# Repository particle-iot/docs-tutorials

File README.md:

# docs-tutorials

Tutorials, sample code, and sample designs used in the documentation [docs.particle.io](https://docs.particle.io).

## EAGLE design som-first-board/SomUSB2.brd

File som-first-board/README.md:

# SoM First Board

The tutorial can be found here: [https://docs.particle.io/tutorials/hardware-projects/som-first-board/](https://docs.particle.io/tutorials/hardware-projects/som-first-board/)

This repository contains the Eagle design files for the board used in the example.

- SomUSB2.sch - Schematic file for EagleCAD
- SomUSB2.brd - Board file for EagleCAD
- schematic.pdf - Schematic (PDF)
- board.pdf - Board (PDF)
- SomUSB1.lbr - Eagle library file with all of the parts used in the design
- SomUSB2v2.zip - Gerber files

### Version History

#### 2024-01-22 (v3)

- M.2 pin 40 should be D3 and M.2 pin 42 should be D2. These were reversed previously, however
this sample board does not use the pins.

#### 2020-03-30 (v2)

- Changed R8 from 158K to 150K to change 3V7 to 3V8. The voltage increase to 3.875V adds an extra safety margin for some modem modules.

#### 2019-10-24

- Updated M.2 standoff

#### 2019-05-20

- Initial version

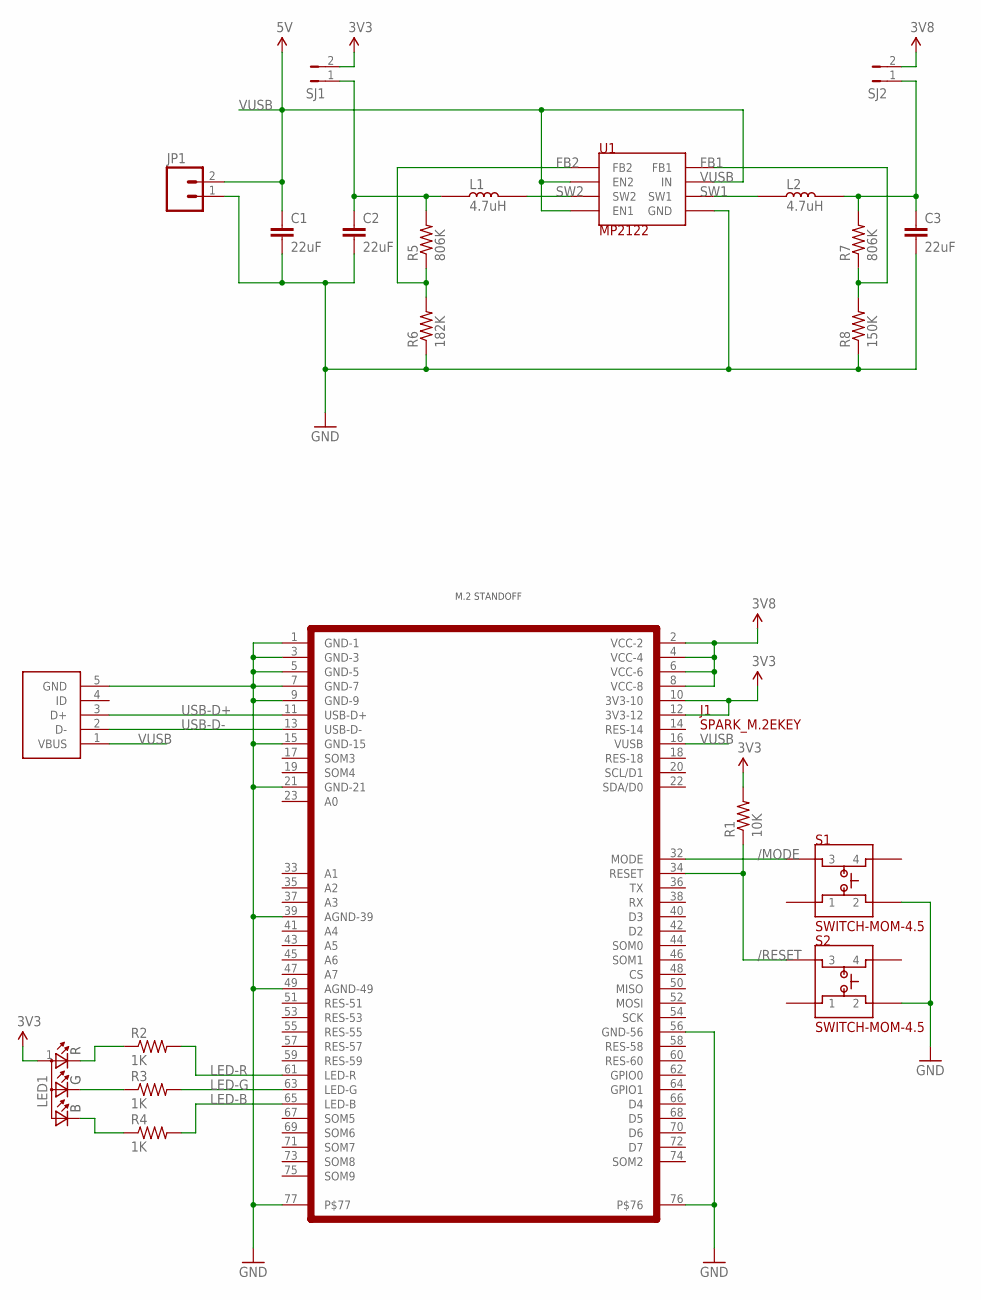
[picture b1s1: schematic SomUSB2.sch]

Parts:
C1, C2, C3: 22uF; 0805
J1: SPARK_M.2EKEY; SPARK_M.2EKEY-LESS-CREAM
JP1: M02PTH; 1X02
L1, L2: 4.7uH; 1008-BOURNS
LED1: LED-RGB-CREE-SMD
R1: 10K; 0603-RES
R2, R3, R4: 1K; 0603-RES
R5, R7: 806K; 0603-RES
R6: 182K; 0603-RES
R8: 150K; 0603-RES
S1, S2: SWITCH-MOM-4.5
SJ1, SJ2: JUMPER-PTH-2-NO; PTH-JUMPER-2-NO_NO_SILK
U1: MP2122; TSOT23-8-MPS
U$1: M2-STANDOFF
U$3: USB-MICRO-B-SOCKET-AMPHENOL; USB-B-SMT-AMPHENOL

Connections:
3V3: J1.10 (3V3-10), J1.12 (3V3-12), LED1.1 (A), R1.2, SJ1.2
3V3-REG: C2.1, L1.1, R5.2, SJ1.1
3V8: J1.2 (VCC-2), J1.4 (VCC-4), J1.6 (VCC-6), J1.8 (VCC-8), SJ2.2
3V8-REG: C3.1, L2.2, R7.2, SJ2.1
/MODE: J1.32 (MODE), S1.3
/RESET: J1.34 (RESET), R1.1, S2.3
FB1: R7.1, R8.2, U1.8 (FB1)
FB2: R5.1, R6.2, U1.1 (FB2)
GND: C1.2, C2.2, C3.2, J1.1 (GND-1), J1.3 (GND-3), J1.5 (GND-5), J1.7 (GND-7), J1.9 (GND-9), J1.15 (GND-15), J1.21 (GND-21), J1.39 (AGND-39), J1.49 (AGND-49), J1.56 (GND-56), J1.76, J1.77, JP1.1, R6.1, R8.1, S1.2, S2.2, U1.5 (GND), U$3.5 (GND)
LED-B: J1.65 (LED-B), R4.2
LED-G: J1.63 (LED-G), R3.2
LED-R: J1.61 (LED-R), R2.2
unnamed: LED1.3 (G), R3.1
unnamed: LED1.4 (R), R2.1
unnamed: LED1.2 (B), R4.1
SW1: L2.1, U1.6 (SW1)
SW2: L1.2, U1.3 (SW2)
USB-D+: J1.11 (USB-D+), U$3.3 (D+)
USB-D-: J1.13 (USB-D-), U$3.2 (D-)
VUSB: C1.1, J1.16 (VUSB), JP1.2, U1.2 (EN2), U1.4 (EN1), U1.7 (IN), U$3.1 (VBUS)

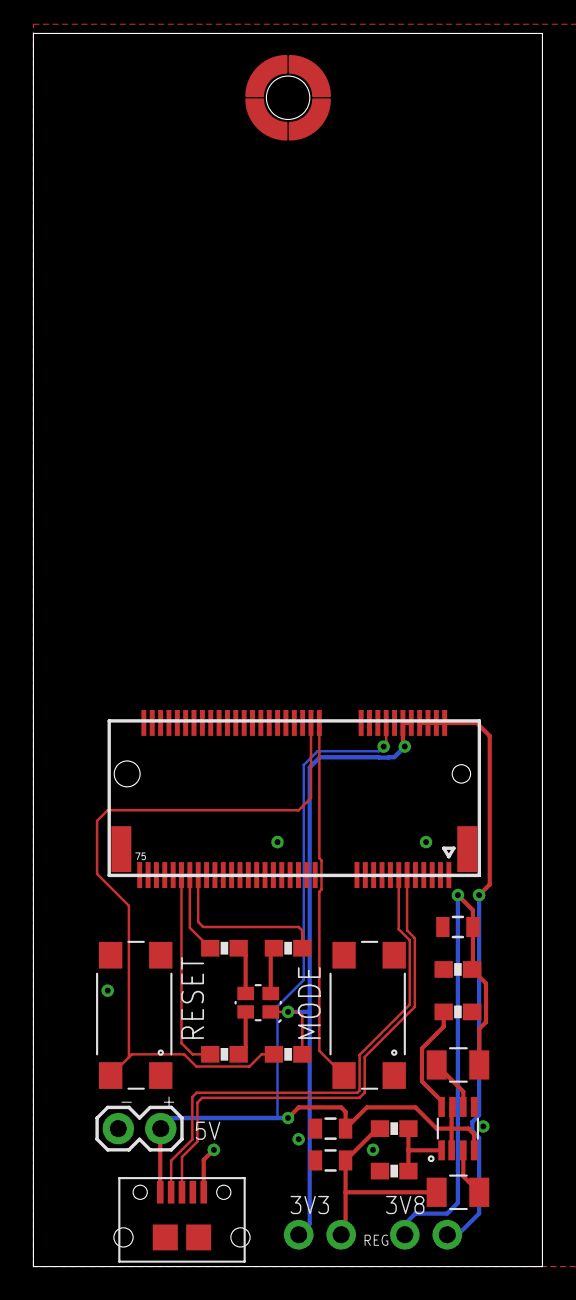
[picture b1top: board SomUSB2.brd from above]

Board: 2 copper layers, 30.5 x 73.8 mm, 23 parts (0 on the bottom side), 20 nets.

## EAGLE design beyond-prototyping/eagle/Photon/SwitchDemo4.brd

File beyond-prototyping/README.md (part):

# Upping your prototyping game

*Going from solderless breadboards to SMD components across Particle devices*

### Solderless breadboards 1

One of the most common ways to start building your project is to use a solderless breadboard. Here's my switch demo circuit in pure prototyping mode. There's an [RGB LED](https://www.sparkfun.com/products/10821) and an [LED button](https://www.sparkfun.com/products/10440) to the right of the Argon. This version uses long flexible wires, which are easy to set up and are easily reusable.

This is the schematic for the circuit:

Because the LED button switch pins don't line up with the holes on a solderless breadboard (0.1"), there's a [small adapter board](https://www.sparkfun.com/products/10467).

#### Bill of Materials (BOM)

| Quan | Item | Example | Price | 
| :--: | :--- | :--- | ---: |
| 1 | LED tactile button | [SparkFun](https://www.sparkfun.com/products/10440) | $2.10 |
| 1 | Button adapter | [SparkFun](https://www.sparkfun.com/products/10467) | $1.50 | 
| 1 | RGB LED | [SparkFun](https://www.sparkfun.com/products/10821) | $2.05 |
| 2 | 10 ohm resistor | | | 
| 2 | 100 ohm resistor | | |

### Solderless breadboards 2

One way to dress up your project is to switch to solid wires. It's a bit more work, but it certainly looks more professional and is good for projects you want to keep as-is.

I used a combination of [pre-formed wires](https://www.amazon.com/gp/product/B07WLPN929/ref=ppx_yo_dt_b_search_asin_title) and wires I cut, stripped, and bent to length from a [SparkFun hookup wire kit](https://www.sparkfun.com/products/11367).

### Perma-Proto

Once you've built and tested your solderless breadboard with solid wires, the next step up is an [Adafruit Perma-Proto](https://www.adafruit.com/product/1609) board. It has the same wiring as a solderless breadboard, but you solder the wires in place.

Resist the temptation to solder your device in place. Always use sockets, otherwise it's really a pain to troubleshoot or swap out the device if a problem occurs.

- Gen 3 feather (Argon, Boron, Xenon): 1x [12-pin](https://www.digikey.com/product-detail/en/sullins-connector-solutions/PPTC121LFBN-RC/S6100-ND/807231), 1x [16-pin](https://www.digikey.com/product-detail/en/sullins-connector-solutions/PPTC161LFBN-RC/S7014-ND/810154)
- Photon: 2x [12-pin](https://www.digikey.com/product-detail/en/sullins-connector-solutions/PPTC121LFBN-RC/S6100-ND/807231)
- Electron: 2x [18-pin](https://www.digikey.com/product-detail/en/sullins-connector-solutions/PPTC181LFBN-RC/S7016-ND/810156)

Note that you should use these headers or ones like them. The spacing between rows is not the same as most IC sockets. Plus, the pins on Particle devices are square, not the flat like IC chip leads, and wouldn't fit securely in an IC socket.

All you need to do is transfer over the component and wires and solder them to the board!

### Feather prototyping board

One of the nice features of the Gen 3 prototyping devices is the use of the [Adafruit Feather form-factor](https://learn.adafruit.com/adafruit-feather/feather-specification). Not only does this allow the devices to be easily swapped, but there are a large number of accessories like displays, GPS modules, and sensors already built in the Feather form-factor. Using a doubler, tripler, or quadrupler, you can add these to your project with no loose wires and no soldering!

However, sometimes you want something a little more custom. In this version, instead of using a big perma-proto board, I used a little FeatherWing solder prototype board. This is one in a Feather Doubler with an Argon:

And the board itself:

### Feather PTH board (through-hole components)

While the previous soldered boards all work fine, you can really make things look professional with a custom printed circuit board. This one uses hand-soldered through-hole components. It's referred to a PTH, plated through-hole.

I created the board schematic in [Eagle CAD](https://www.autodesk.com/products/eagle/overview). This small two-layer board can be done in the free version of Eagle CAD. The various schematic and board files are in the **eagle** directory in the Github repository.

The other part is creating the board file, which includes the actual placement of the components and the traces, which take the place of the wires. Here's by board file in Eagle.

I ordered these board from [OshPark](https://oshpark.com). 

Here are the components soldered in place. It's way faster to solder the components onto a circuit board than mess with all of the individual wires. And it looks so neat and clean!

### Feather SMD components board

The next step up is to switch to use SMD (surface mount device) components. The switch button is still through-hole soldered, but the resistors and LED are SMD. 

As your designs get more complex, being able to use smaller SMD components saves space and is actually easier than hand soldering once you get the hang of it. Also, many modern ICs are only available in SMD form-factor. The SMD RGB LED in this design is significantly less expensive than the PTH LED used above ($0.19 vs. $2.05).

The SMD LED uses different current-limiting resistors but the schematic is otherwise the same.

In order to assemble a SMD board, you'll use solder paste. I like this kind in a little syringe. This is [low-temperature solder paste](https://www.amazon.com/gp/product/B017RSGPI8/ref=ppx_yo_dt_b_search_asin_title), which is easy to work with and is lead-free.

Like the previous board, I ordered it from [OshPark](https://oshpark.com). Using the small syringe tip I put a little dot of solder on all of the SMD pads.

The next step is to place the components on the board. I like to use forceps and a dental pick. Some people prefer tweezers.

The the board goes into the reflow oven. This is an inexpensive T-962 which works fine for simple boards. 

There are a number of DIY techniques including using a skillet or baking them in a toaster oven, but using a real reflow oven is more accurate.

And here's the board after reflow soldering:

#### Bill of Materials (BOM)

| Quan | Item | Example | Price | 
| :--: | :--- | :--- | ---: |
| 1 | LED tactile button | [SparkFun](https://www.sparkfun.com/products/10440) | $2.10 |
| 1 | RGB LED | [Cree CLMVC-FKA-CL1D1L71BB7C3C3](https://www.digikey.com/product-detail/en/cree-inc/CLMVC-FKA-CL1D1L71BB7C3C3/CLMVC-FKA-CL1D1L71BB7C3C3CT-ND/9094273) | $0.19 |
|   | Male Header Pins | [Sullins PRPC040SAAN-RC](https://www.digikey.com/product-detail/en/PRPC040SAAN-RC/S1011EC-40-ND/2775214) |  |
| 2 | 33 ohm resistor 0603 | [Panasonic](https://www.digikey.com/product-detail/en/panasonic-electronic-components/ERJ-3EKF33R0V/P33.0HCT-ND/1746765) | | 
| 2 | 68 ohm resistor 0603 | [Panasonic](https://www.digikey.com/product-detail/en/panasonic-electronic-components/ERJ-3EKF68R0V/P68.0HCT-ND/1746805) | |

### Wing under-mount board

You don't need to make your boards into the actual FeatherWing form-factor. You can make an under-mount board as well. This is handy for larger designs. 

The schematic is the same, but the Eagle board layout is different:

#### Bill of Materials (BOM)

| Quan | Item | Example | Price | 
| :--: | :--- | :--- | ---: |
| 1 | LED tactile button | [SparkFun](https://www.sparkfun.com/products/10440) | $2.10 |
| 1 | RGB LED | [Cree CLMVC-FKA-CL1D1L71BB7C3C3](https://www.digikey.com/product-detail/en/cree-inc/CLMVC-FKA-CL1D1L71BB7C3C3/CLMVC-FKA-CL1D1L71BB7C3C3CT-ND/9094273) | $0.19 |
| 1 | 12-pin header | [Sullins](https://www.digikey.com/product-detail/en/sullins-connector-solutions/PPTC121LFBN-RC/S6100-ND/807231) | $0.78 |
| 1 | 16-pin header | [Sullins](https://www.digikey.com/product-detail/en/sullins-connector-solutions/PPTC161LFBN-RC/S7014-ND/810154) | $0.98 |
| 2 | 33 ohm resistor 0603 | [Panasonic](https://www.digikey.com/product-detail/en/panasonic-electronic-components/ERJ-3EKF33R0V/P33.0HCT-ND/1746765) | | 
| 2 | 68 ohm resistor 0603 | [Panasonic](https://www.digikey.com/product-detail/en/panasonic-electronic-components/ERJ-3EKF68R0V/P68.0HCT-ND/1746805) | |

### Photon (Gen 2 Wi-Fi)

The Photon board is a lot like the under-mount FeatherWing board, but it has two [12-pin headers](https://www.digikey.com/product-detail/en/sullins-connector-solutions/PPTC121LFBN-RC/S6100-ND/807231) to fit a Photon.

The Gen 2 devices (Photon, P1, Electron, and E Series) use different pins because the STM32F205 processor supports PWM for the RGB LED on different pins. Thus the schematic is slightly different:

#### Bill of Materials (BOM)

| Quan | Item | Example | Price | 
| :--: | :--- | :--- | ---: |
| 1 | LED tactile button | [SparkFun](https://www.sparkfun.com/products/10440) | $2.10 |
| 1 | RGB LED | [Cree CLMVC-FKA-CL1D1L71BB7C3C3](https://www.digikey.com/product-detail/en/cree-inc/CLMVC-FKA-CL1D1L71BB7C3C3/CLMVC-FKA-CL1D1L71BB7C3C3CT-ND/9094273) | $0.19 |
| 2 | 12-pin header | [Sullins](https://www.digikey.com/product-detail/en/sullins-connector-solutions/PPTC121LFBN-RC/S6100-ND/807231) | $0.78 |
| 2 | 33 ohm resistor 0603 | [Panasonic](https://www.digikey.com/product-detail/en/panasonic-electronic-components/ERJ-3EKF33R0V/P33.0HCT-ND/1746765) | | 
| 2 | 68 ohm resistor 0603 | [Panasonic](https://www.digikey.com/product-detail/en/panasonic-electronic-components/ERJ-3EKF68R0V/P68.0HCT-ND/1746805) | |

### Electron (Gen 2 cellular)

The Electron board is nearly identical to the Photon, except it has [18-pin headers](https://www.digikey.com/product-detail/en/sullins-connector-solutions/PPTC181LFBN-RC/S7016-ND/810156) instead of 12-pin. In fact, you can plug in a Photon into the Electron board if you align the pins on the left, leaving the unused socket pins on the right closest to the switch.

#### Bill of Materials (BOM)

| Quan | Item | Example | Price | 
| :--: | :--- | :--- | ---: |
| 1 | LED tactile button | [SparkFun](https://www.sparkfun.com/products/10440) | $2.10 |
| 1 | RGB LED | [Cree CLMVC-FKA-CL1D1L71BB7C3C3](https://www.digikey.com/product-detail/en/cree-inc/CLMVC-FKA-CL1D1L71BB7C3C3/CLMVC-FKA-CL1D1L71BB7C3C3CT-ND/9094273) | $0.19 |
| 2 | 18-pin header | [Sullins](https://www.digikey.com/product-detail/en/sullins-connector-solutions/PPTC181LFBN-RC/S7016-ND/810156) | $1.10 |
| 2 | 33 ohm resistor 0603 | [Panasonic](https://www.digikey.com/product-detail/en/panasonic-electronic-components/ERJ-3EKF33R0V/P33.0HCT-ND/1746765) | | 
| 2 | 68 ohm resistor 0603 | [Panasonic](https://www.digikey.com/product-detail/en/panasonic-electronic-components/ERJ-3EKF68R0V/P68.0HCT-ND/1746805) | |

### P1 (Gen 2 Wi-Fi SMD)

Making a board for the P1 module is more difficult than the devices we've used so far. It's recommended that you include:

- RGB LED (the status one)
- RESET and MODE buttons
- USB connector
- 3.3V Regulator

To match the other boards, this design includes a second RGB LED and LED button switch. It also includes a 10-pin micro SWD/JTAG connector and the blue D7 LED (optional).

Schematic

Board 

#### Bill of Materials (BOM)

| Quan | Item | Example | Price | 
| :--: | :--- | :--- | ---: |
| 1 | LED tactile button | [SparkFun](https://www.sparkfun.com/products/10440) | $2.10 |
| 2 | RGB LED | [Cree CLMVC-FKA-CL1D1L71BB7C3C3](https://www.digikey.com/product-detail/en/cree-inc/CLMVC-FKA-CL1D1L71BB7C3C3/CLMVC-FKA-CL1D1L71BB7C3C3CT-ND/9094273) | $0.19 |
| 4 | 33 ohm resistor 0603 | [Panasonic](https://www.digikey.com/product-detail/en/panasonic-electronic-components/ERJ-3EKF33R0V/P33.0HCT-ND/1746765) | | 
| 4 | 68 ohm resistor 0603 | [Panasonic](https://www.digikey.com/product-detail/en/panasonic-electronic-components/ERJ-3EKF68R0V/P68.0HCT-ND/1746805) | |
| 1 | 100 ohm resistor 0603 | [Panasonic](https://www.digikey.com/product-detail/en/panasonic-electronic-components/ERJ-3GEYJ101V/P100GCT-ND/134714) | |
| 2| 10K ohm resistor 0603 | [Panasonic](https://www.digikey.com/product-detail/en/panasonic-electronic-components/ERJ-PA3J103V/P10KBZCT-ND/5036237) | |
| 3 | 0.1uF capacitor 0603 | [Panasonic](https://www.digikey.com/product-detail/en/murata-electronics-north-america/GRM188R71C104KA01D/490-1532-1-ND/587771) | |
| 1 | 4.7uF capacitor 0603 | [Panasonic](https://www.digikey.com/product-detail/en/murata-electronics-north-america/GRM188R60J475KE19J/490-6407-1-ND/3845604) | |
| 4 | 10uF capacitor 0805 | [Panasonic](https://www.digikey.com/product-detail/en/murata-electronics-north-america/GRM21BR61C106KE15L/490-3886-1-ND/965928) | |
| 1 | MCP1825ST voltage regulator | [Microchip](https://www.digikey.com/product-detail/en/microchip-technology/MCP1825ST-3302E-DB/MCP1825ST-3302E-DBCT-ND/5013522) | $0.53 |
| 1 | USB Micro B connector | [Amphenol FCI 10118194-0001LF](https://www.digikey.com/products/en?keywords=609-4618-1-nd) | $0.42|
| 1 | 10-pin JTAG Connector | [Samtek SAM8796-ND](https://www.digikey.com/products/en?keywords=SAM8796-ND) | $2.90 |
| 2 | Tactile switch | [C&K PTS645SH50SMTR92](https://www.digikey.com/product-detail/en/c-k/PTS645SH50SMTR92-LFS/CKN9085CT-ND/1146817) | $0.21 |

### E Series (Gen 2 cellular SMD)

The E Series Gen 2 cellular module is about the same level of effort as the P1. It has a built-in voltage regulator and PMIC, but you need to add a battery connector.

- RGB LED (the status one)
- RESET and MODE buttons
- USB connector
- Battery connector
- Charge LED (I forgot to add this in the design here)

Schematic:

Board:

#### Bill of Materials (BOM)

| Quan | Item | Example | Price | 
| :--: | :--- | :--- | ---: |
| 1 | LED tactile button | [SparkFun](https://www.sparkfun.com/products/10440) | $2.10 |
| 2 | RGB LED | [Cree CLMVC-FKA-CL1D1L71BB7C3C3](https://www.digikey.com/product-detail/en/cree-inc/CLMVC-FKA-CL1D1L71BB7C3C3/CLMVC-FKA-CL1D1L71BB7C3C3CT-ND/9094273) | $0.19 |
| 4 | 33 ohm resistor 0603 | [Panasonic](https://www.digikey.com/product-detail/en/panasonic-electronic-components/ERJ-3EKF33R0V/P33.0HCT-ND/1746765) | | 
| 4 | 68 ohm resistor 0603 | [Panasonic](https://www.digikey.com/product-detail/en/panasonic-electronic-components/ERJ-3EKF68R0V/P68.0HCT-ND/1746805) | |
| 1 | 10K ohm resistor 0603 | [Panasonic](https://www.digikey.com/product-detail/en/panasonic-electronic-components/ERJ-PA3J103V/P10KBZCT-ND/5036237) | |
| 1 | USB Micro B connector | [Amphenol FCI 10118194-0001LF](https://www.digikey.com/products/en?keywords=609-4618-1-nd) | $0.42|
| 2 | Tactile switch | [E-Switch TL3305AF160QG](https://www.digikey.com/product-detail/en/e-switch/TL3305AF160QG/EG5350CT-ND/5816195) | $0.20 |
| 1 | JST-PH battery connector | [JST B2B-PH-K-S-LF-SN](https://www.digikey.com/product-detail/en/jst-sales-america-inc/B2B-PH-K-S-LF-SN/455-1704-ND/926611) | $0.17 | 

## Publish Demo

The publish demo uses publish and subscribe to communicate between demo boards. Each device has its own button color programmed in its device firmware. Pressing the button publishes the color, which shows up on all of the other devices.

It works between Wi-Fi and cellular devices, across Gen 2 and Gen 3 devices!

<video width="640" height="360" controls >
  <source src="images/publish.mp4" type="video/mp4">
</video>

```
#include "Particle.h"

#include "LedSwitchRK.h"

SYSTEM_THREAD(ENABLED);

SerialLogHandler logHandler;

#if HAL_PLATFORM_MESH
const uint16_t STATUS_RED = A0;
const uint16_t STATUS_GREEN = A1;
const uint16_t STATUS_BLUE = A2;
const uint16_t SWITCH_PIN = D6;
const uint16_t SWITCH_LED_PIN = D5;
#else
const uint16_t STATUS_RED = WKP;
const uint16_t STATUS_GREEN = D3;
const uint16_t STATUS_BLUE = D2;
const uint16_t SWITCH_PIN = D5;
const uint16_t SWITCH_LED_PIN = D4;
#endif

const uint32_t MY_COLOR = 0x00ff00;
// 0xff0000 = red
// 0x00ff00 = green
// 0x0000ff = blue
// 0xFFFF00 = yellow
// 0xFF00FF = magenta
// 0xFFFFFF = white

const char *EVENT_NAME = "switchDemoSet";

LedSwitch ledSwitch(SWITCH_LED_PIN, SWITCH_PIN); // led, switch

void switchDemoHandler(const char *event, const char *data);
void setColor(uint32_t color);

const unsigned long BUTTON_ON_PERIOD = 2000;
unsigned long lastButtonOn = 0;

void setup() {
	pinMode(STATUS_RED, OUTPUT);
	pinMode(STATUS_GREEN, OUTPUT);
	pinMode(STATUS_BLUE, OUTPUT);
	setColor(0x000000); // black/off

	Particle.subscribe(EVENT_NAME, switchDemoHandler, MY_DEVICES);
}

void loop() {
	if (ledSwitch.pressed()) {
		Log.info("button pressed");
		setColor(MY_COLOR);

		lastButtonOn = millis();
		ledSwitch.ledOn();

		char buf[32];
		snprintf(buf, sizeof(buf), "%06lx", MY_COLOR);
		Particle.publish(EVENT_NAME, buf, PRIVATE);
	}

	if (lastButtonOn != 0 && millis() - lastButtonOn >= BUTTON_ON_PERIOD) {
		lastButtonOn = 0;
		ledSwitch.ledOff();
	}

}

void switchDemoHandler(const char *event, const char *data) {
	uint32_t rgbColor;

	if (sscanf(data, "%06lx", &rgbColor) == 1) {
		Log.info("received color 0x%06lx", rgbColor);
		setColor(rgbColor);
	}
	else {
		Log.info("invalid data %s", data);
	}
}

void setColor(uint32_t color) {
	uint8_t red = (uint8_t)((color >> 16) & 0xff);
	uint8_t green = (uint8_t)((color >> 8) & 0xff);
	uint8_t blue = (uint8_t)(color & 0xff);

	// The LED is common anode, so for analogWrite()
	// 0 = full on
	// 128 = half on
	// 255 = off
	//
	// This is opposite of the normal meaning of the LED intensity (0 = off, 255 = full on) so
	// the 255 - factor here.
	analogWrite(STATUS_RED, 255 - red);
	analogWrite(STATUS_GREEN, 255 - green);
	analogWrite(STATUS_BLUE, 255 - blue);
}
```

The code depends on the **LedSwitchRK** library.

```
dependencies.LedSwitchRK=0.0.2
```

## Test Firmware

To make it easier to test a single device, I use the test firmware below.

It defaults to fading between colors on the RGB LED. Pressing the button toggles between the various primary RGB colors, and also toggles the LED button on and off.

```
#include "Particle.h"

#include "LedSwitchRK.h"

#include <cmath>

SYSTEM_THREAD(ENABLED);

SerialLogHandler logHandler;

//                         red       green     blue      yellow    cyan      magenta   white
uint32_t testColors[7] = { 0xFF0000, 0x00FF00, 0x0000FF, 0xFFFF00, 0x00FFFF, 0xFF00FF, 0xFFFFFF };

#if HAL_PLATFORM_MESH
const uint16_t STATUS_RED = A0;
const uint16_t STATUS_GREEN = A1;
const uint16_t STATUS_BLUE = A2;
const uint16_t SWITCH_PIN = D6;
const uint16_t SWITCH_LED_PIN = D5;
#else
const uint16_t STATUS_RED = WKP;
const uint16_t STATUS_GREEN = D3;
const uint16_t STATUS_BLUE = D2;
const uint16_t SWITCH_PIN = D5;
const uint16_t SWITCH_LED_PIN = D4;
#endif

LedSwitch ledSwitch(SWITCH_LED_PIN, SWITCH_PIN); // led, switch

const unsigned long CHANGE_PERIOD_MS = 10;
unsigned long lastChange = 0;
size_t curColor = -1;
int curDegree = 0;

int ledToggle(String cmd);
void setColor(uint32_t color);
uint32_t HSVtoRGB(int H, double S, double V);

void setup() {
	Wire.begin();

	pinMode(STATUS_RED, OUTPUT);
	pinMode(STATUS_GREEN, OUTPUT);
	pinMode(STATUS_BLUE, OUTPUT);

	Particle.function("led", ledToggle);
}

void loop() {
	if (ledSwitch.pressed()) {
		Log.info("Button pressed");
		ledSwitch.ledToggle();

		if (++curColor >= (sizeof(testColors) / sizeof(testColors[0]))) {
			// -1 = rainbow
			// 0 - n = color in array testColors[curColor]
			curColor = -1;
		}
		else {
			setColor(testColors[curColor]);
		}
	}

	if (curColor == -1) {
		// Rainbows
		if (millis() - lastChange >= CHANGE_PERIOD_MS) {
			lastChange = millis();

			// Use the degrees as the hue in the HSV color space. That's the direction
			// you are pointing on the color wheel.
			//
			// 1.0 is the saturation. 0.0 is at the center of the color wheel (dark) and
			// 1.0 is the outer edge of the color wheel.
			//
			// 0.6 is the value or brightness. 1.0 is the maximum but I turned it down
			// a bit to be less blinding.
			uint32_t color = HSVtoRGB(curDegree, 1.0, 0.6);
			setColor(color);

			if (++curDegree >= 360) {
				curDegree = 0;
			}
		}
	}

}

int ledToggle(String cmd) {

	Log.info("toggling LED from Particle function");
	ledSwitch.ledToggle();

	return 0;
}

void setColor(uint32_t color) {
	uint8_t red = (uint8_t)((color >> 16) & 0xff);
	uint8_t green = (uint8_t)((color >> 8) & 0xff);
	uint8_t blue = (uint8_t)(color & 0xff);

	// The LED is common anode, so for analogWrite()
	// 0 = full on
	// 128 = half on
	// 255 = off
	//
	// This is opposite of the normal meaning of the LED intensity (0 = off, 255 = full on) so
	// the 255 - factor here.
	analogWrite(STATUS_RED, 255 - red);
	analogWrite(STATUS_GREEN, 255 - green);
	analogWrite(STATUS_BLUE, 255 - blue);
}

// Modified from:
// https://gist.github.com/kuathadianto/200148f53616cbd226d993b400214a7f
// H(Hue): 0 - 360 degree (integer)
// S(Saturation): 0 - 1.00 (double)
// V(Value): 0 - 1.00 (double)
uint32_t HSVtoRGB(int H, double S, double V) {
	double C = S * V;
	double X = C * (1 - std::abs(std::fmod(H / 60.0, 2) - 1));
	double m = V - C;
	double Rs, Gs, Bs;

	if(H >= 0 && H < 60) {
		Rs = C;
		Gs = X;
		Bs = 0;
	}
	else if(H >= 60 && H < 120) {
		Rs = X;
		Gs = C;
		Bs = 0;
	}
	else if(H >= 120 && H < 180) {
		Rs = 0;
		Gs = C;
		Bs = X;
	}
	else if(H >= 180 && H < 240) {
		Rs = 0;
		Gs = X;
		Bs = C;
	}
	else if(H >= 240 && H < 300) {
		Rs = X;
		Gs = 0;
		Bs = C;
	}
	else {
		Rs = C;
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
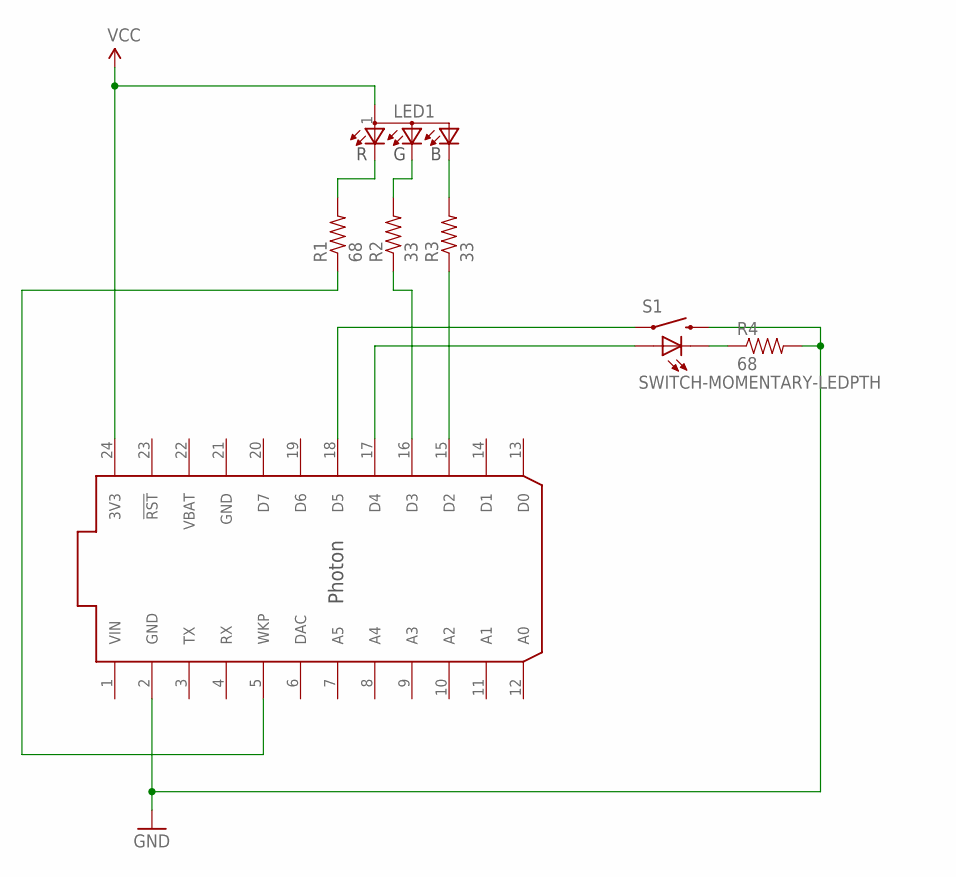
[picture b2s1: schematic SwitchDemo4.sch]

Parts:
LED1: LED-RGB-CREE-SMD
R1, R4: 68; 0603-RES
R2, R3: 33; 0603-RES
S1: SWITCH-MOMENTARY-LEDPTH; TACTILE-PTH-LED-12MM
U$1: PHOTON; PHOTON-SMD

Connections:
BLED: LED1.2 (B), R3.2
D2: R3.1, U$1.15 (D2)
D3: R2.1, U$1.16 (D3)
D4: S1.A, U$1.17 (D4)
D5: S1.4 (1), U$1.18 (D5)
GLED: LED1.3 (G), R2.2
GND: R4.2, S1.2, U$1.2 (GND), U$1.21 (GND)
RLED: LED1.4 (R), R1.2
SLED: R4.1, S1.C
VBAT: U$1.22 (VBAT)
VCC: LED1.1 (A), U$1.24 (3V3)
VIN: U$1.1 (VIN)
WKP: R1.1, U$1.5 (WKP)

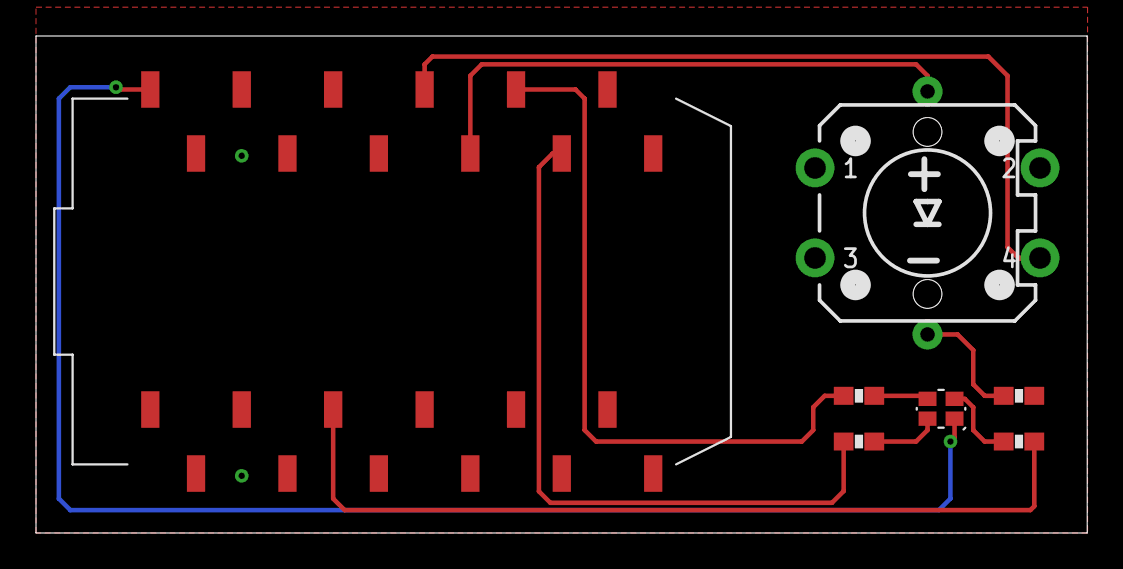
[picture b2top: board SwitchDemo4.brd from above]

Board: 2 copper layers, 58.4 x 27.6 mm, 7 parts (0 on the bottom side), 11 nets.

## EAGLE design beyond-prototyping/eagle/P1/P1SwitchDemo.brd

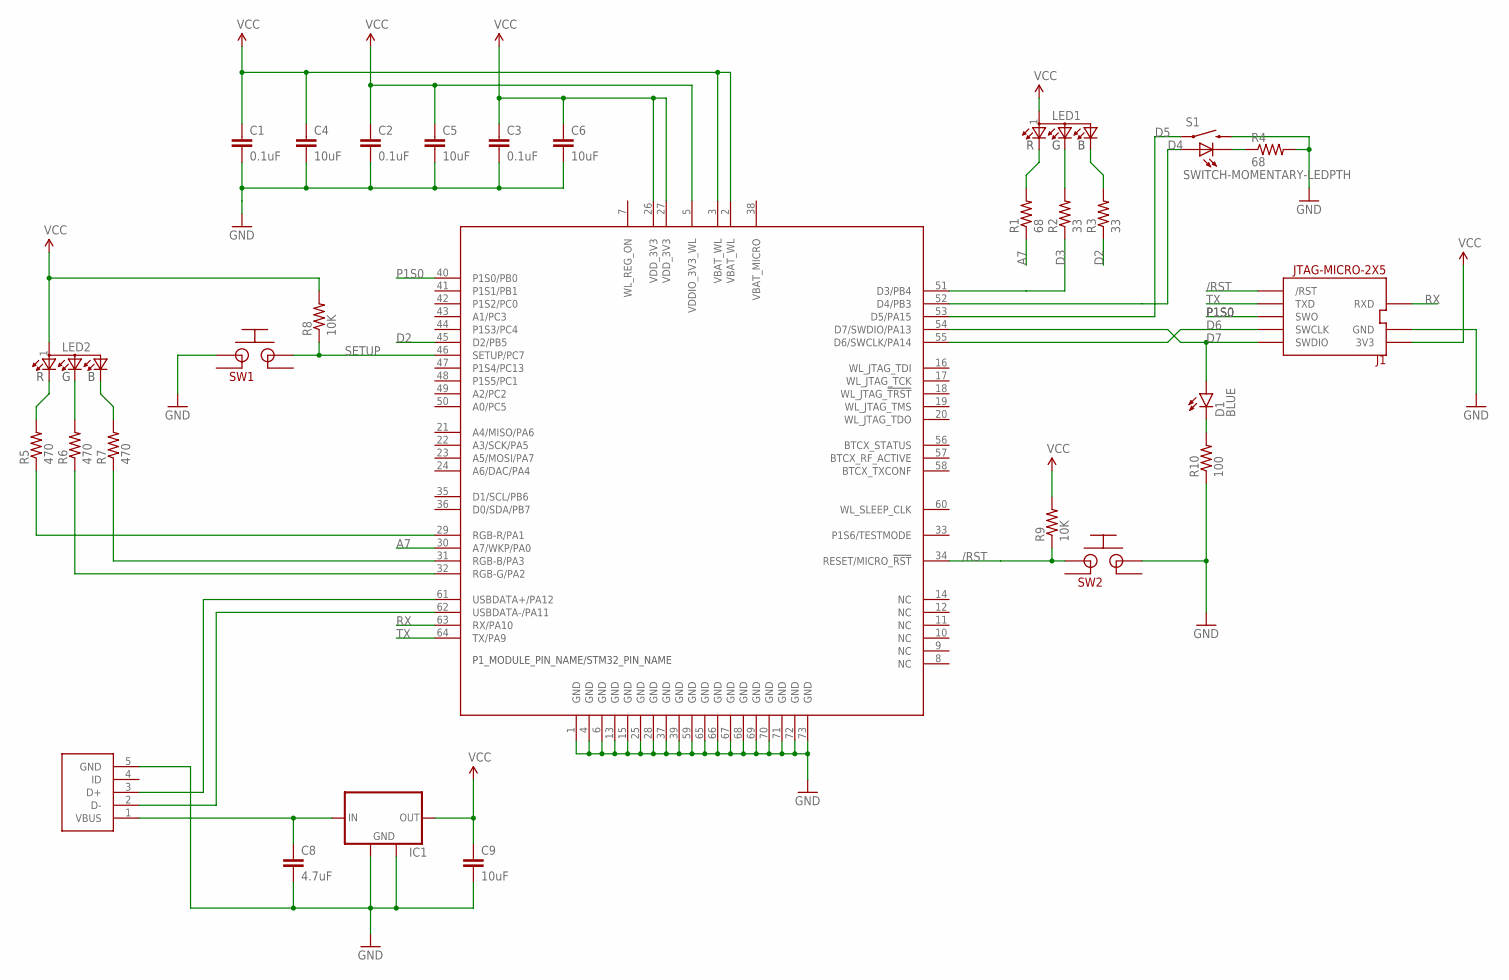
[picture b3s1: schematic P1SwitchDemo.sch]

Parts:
C1, C2, C3: 0.1uF; 0603-CAP
C4, C5, C6, C9: 10uF; 0603-CAP
C8: 4.7uF; 0603-CAP
D1: BLUE; LED-0603
IC1: MCP1825S-SOT223; SOT223
J1: JTAG-MICRO-2X5
LED1, LED2: LED-RGB-CREE-SMD
R1, R4: 68; 0603-RES
R2, R3: 33; 0603-RES
R5, R6, R7: 470; 0603-RES
R8, R9: 10K; 0603-RES
R10: 100; 0603-RES
S1: SWITCH-MOMENTARY-LEDPTH; TACTILE-PTH-LED-12MM
SW1, SW2: SWITCH-PTS645
U$4: USB-MICRO-B-SOCKET-AMPHENOL; USB-B-SMT-AMPHENOL
U$6: P1; WM-N-BM-14

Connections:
/RST: J1.10 (/RST), R9.1, SW2.1, U$6.34 (RESET/MICRO_!RST!)
A7: R1.1, U$6.30 (A7/WKP/PA0)
D2: R3.1, U$6.45 (D2/PB5)
D3: R2.1, U$6.51 (D3/PB4)
D4: S1.A, U$6.52 (D4/PB3)
D5: S1.4 (1), U$6.53 (D5/PA15)
D6: J1.4 (SWCLK), U$6.55 (D6/SWCLK/PA14)
D7: D1.A, J1.2 (SWDIO), U$6.54 (D7/SWDIO/PA13)
GND: C1.2, C2.2, C3.2, C4.2, C5.2, C6.2, C8.2, C9.2, IC1.2 (GND), IC1.4 (GND), J1.3 (GND), J1.5 (GND), J1.9 (GND), R4.2, R10.1, S1.2, SW1.1, SW2.3, U$4.5 (GND), U$6.1 (GND), U$6.4 (GND), U$6.6 (GND), U$6.13 (GND), U$6.15 (GND), U$6.25 (GND), U$6.28 (GND), U$6.37 (GND), U$6.39 (GND), U$6.59 (GND), U$6.65 (GND), U$6.66 (GND), U$6.67 (GND), U$6.68 (GND), U$6.69 (GND), U$6.70 (GND), U$6.71 (GND), U$6.72 (GND), U$6.73 (GND)
IN: C8.1, IC1.1 (IN), U$4.1 (VBUS)
unnamed: LED2.4 (R), R5.2
unnamed: LED2.3 (G), R6.2
unnamed: LED2.2 (B), R7.2
unnamed: D1.C, R10.2
unnamed: LED1.4 (R), R1.2
unnamed: LED1.3 (G), R2.2
unnamed: LED1.2 (B), R3.2
unnamed: R4.1, S1.C
unnamed: U$4.3 (D+), U$6.61 (USBDATA+/PA12)
unnamed: U$4.2 (D-), U$6.62 (USBDATA-/PA11)
P1S0: J1.6 (SWO), U$6.40 (P1S0/PB0)
RGB-B: R7.1, U$6.31 (RGB-B/PA3)
RGB-G: R6.1, U$6.32 (RGB-G/PA2)
RGB-R: R5.1, U$6.29 (RGB-R/PA1)
RX: J1.7 (RXD), U$6.63 (RX/PA10)
SETUP: R8.1, SW1.3, U$6.46 (SETUP/PC7)
TX: J1.8 (TXD), U$6.64 (TX/PA9)
VCC: C1.1, C2.1, C3.1, C4.1, C5.1, C6.1, C9.1, IC1.3 (OUT), J1.1 (3V3), LED1.1 (A), LED2.1 (A), R8.2, R9.2, U$6.2 (VBAT_WL), U$6.3 (VBAT_WL), U$6.5 (VDDIO_3V3_WL), U$6.26 (VDD_3V3), U$6.27 (VDD_3V3)

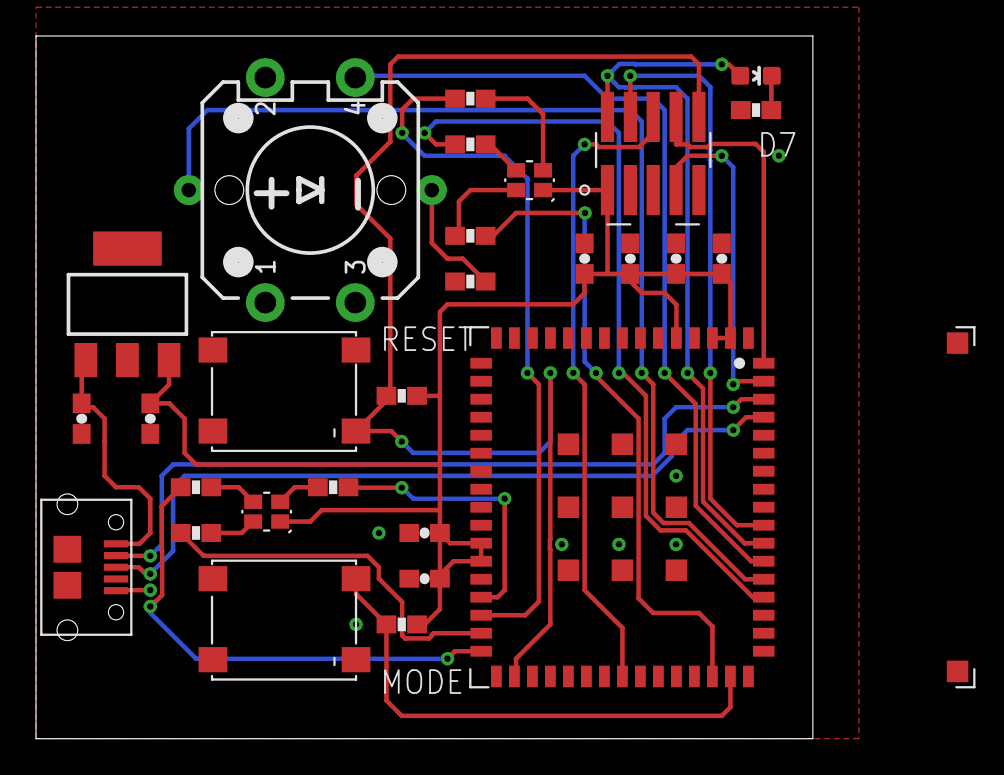
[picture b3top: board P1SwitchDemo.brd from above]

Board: 2 copper layers, 43.2 x 39.0 mm, 28 parts (0 on the bottom side), 28 nets.

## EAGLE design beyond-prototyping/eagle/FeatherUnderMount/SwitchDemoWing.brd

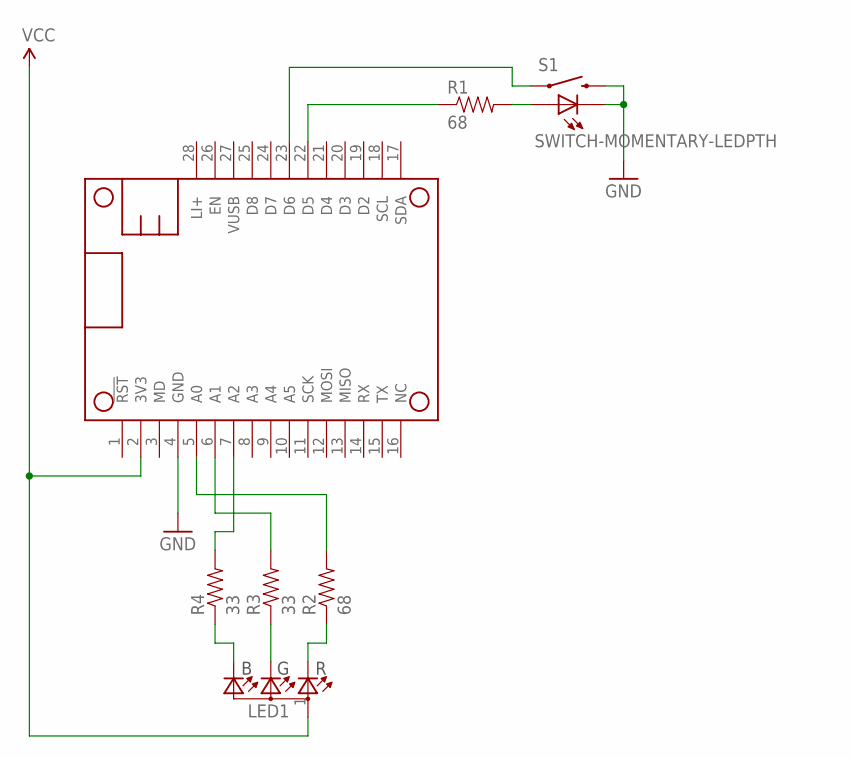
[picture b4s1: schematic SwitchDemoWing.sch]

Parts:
LED1: LED-RGB-CREE-SMD
MS1: PARTICLE_MESH_NODIM; FEATHERWING_NODIM
R1, R2: 68; 0603-RES
R3, R4: 33; 0603-RES
S1: SWITCH-MOMENTARY-LEDPTH; TACTILE-PTH-LED-12MM

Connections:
3V3: LED1.1 (A), MS1.2 (3V3)
A0: MS1.5 (A0), R2.2
A1: MS1.6 (A1), R3.2
A2: MS1.7 (A2), R4.2
D5: MS1.22 (D5), R1.1
D6: MS1.23 (D6), S1.4 (1)
GND: MS1.4 (GND), S1.2, S1.C
LED-B: LED1.2 (B), R4.1
LED-G: LED1.3 (G), R3.1
LED-R: LED1.4 (R), R2.1
unnamed: R1.2, S1.A

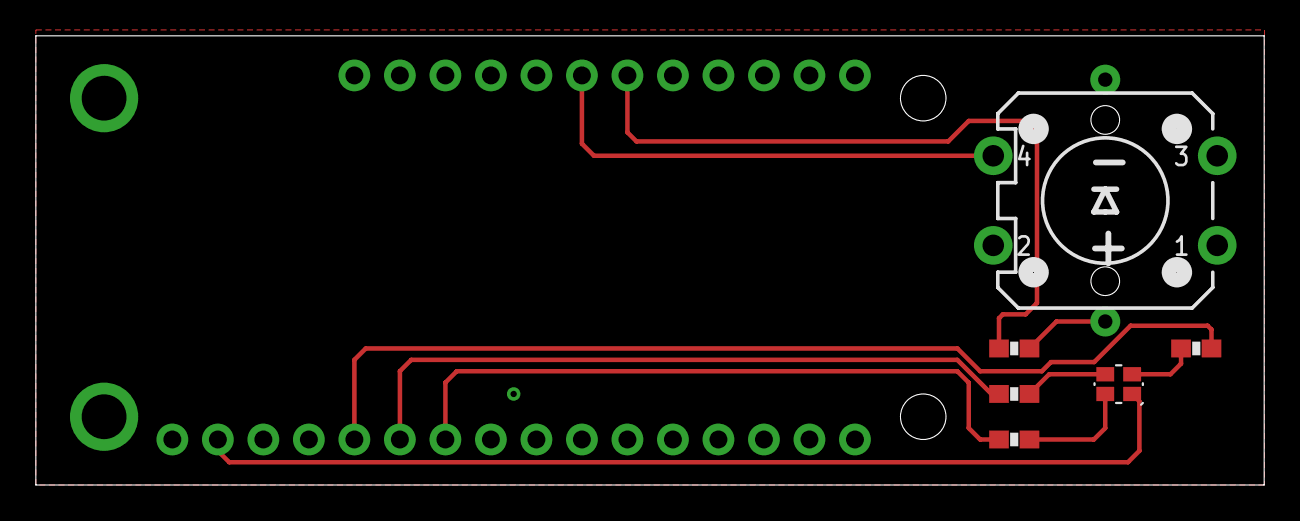
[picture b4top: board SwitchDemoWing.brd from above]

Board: 2 copper layers, 68.6 x 25.1 mm, 7 parts (0 on the bottom side), 11 nets.

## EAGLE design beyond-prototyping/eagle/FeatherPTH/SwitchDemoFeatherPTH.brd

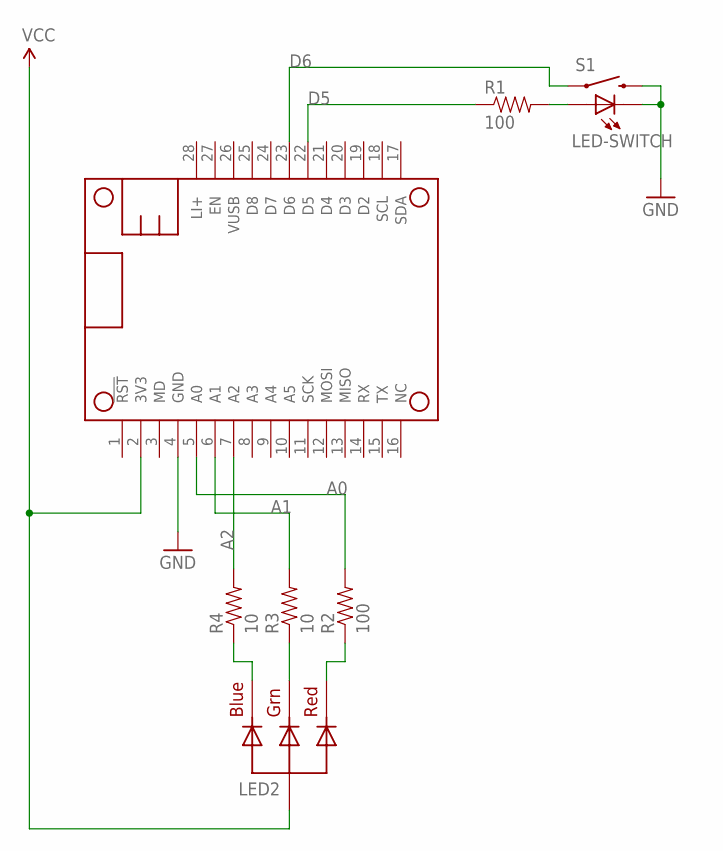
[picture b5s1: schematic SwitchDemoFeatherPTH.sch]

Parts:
LED2: RGBLED_CA-5MM; LED5MMRGB
MS1: PARTICLE_MESH_NODIM; FEATHERWING_NODIM
R1, R2: 100; AXIAL-0.3
R3, R4: 10; AXIAL-0.3
S1: LED-SWITCH; TACTILE-PTH-LED-12MM

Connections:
3V3: LED2.2 (VCC), MS1.2 (3V3)
A0: MS1.5 (A0), R2.P$2 (2)
A1: MS1.6 (A1), R3.P$2 (2)
A2: MS1.7 (A2), R4.P$2 (2)
D5: MS1.22 (D5), R1.P$1 (1)
D6: MS1.23 (D6), S1.4 (1)
GND: MS1.4 (GND), S1.2, S1.C
unnamed: LED2.3 (GREEN), R3.P$1 (1)
unnamed: LED2.4 (BLUE), R4.P$1 (1)
unnamed: R1.P$2 (2), S1.A
unnamed: LED2.1 (RED), R2.P$1 (1)

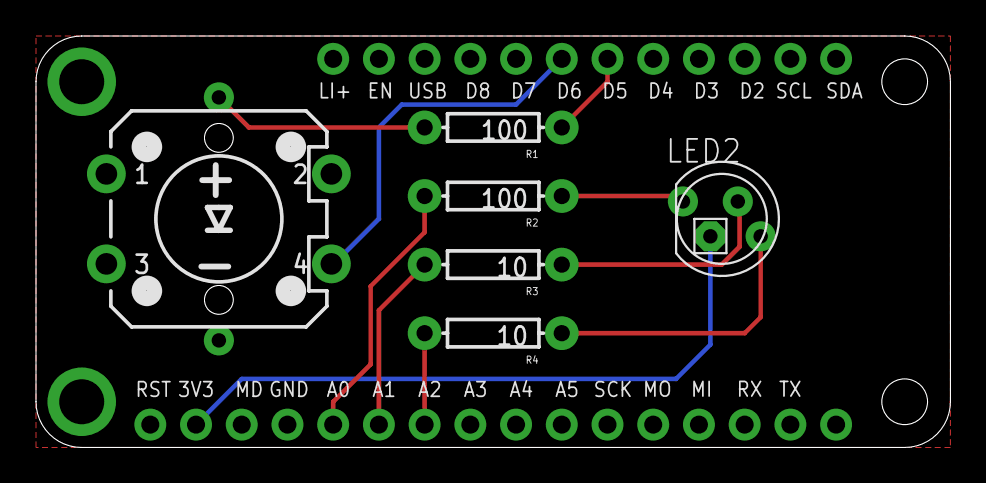
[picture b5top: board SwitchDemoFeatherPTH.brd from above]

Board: 2 copper layers, 50.8 x 22.9 mm, 7 parts (0 on the bottom side), 11 nets.

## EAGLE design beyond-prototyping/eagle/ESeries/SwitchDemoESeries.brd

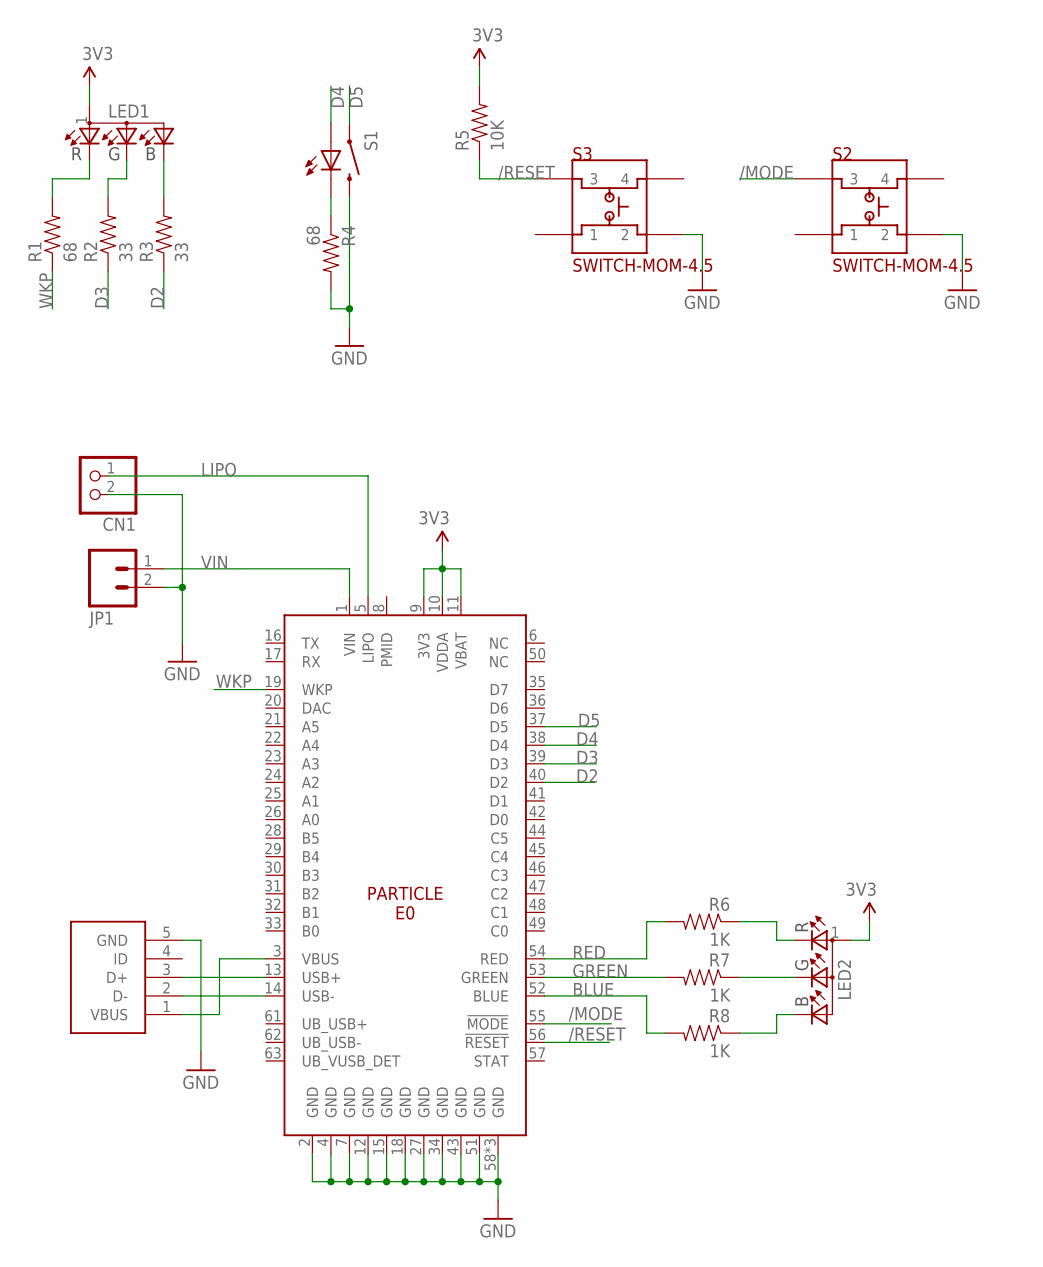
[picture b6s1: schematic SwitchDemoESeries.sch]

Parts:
CN1: JST_2PIN-THM; JST-PH-2-THM
JP1: M02PTH; 1X02
LED1, LED2: LED-RGB-CREE-SMD
R1, R4: 68; 0603-RES
R2, R3: 33; 0603-RES
R5: 10K; 0603-RES
R6, R7, R8: 1K; 0603-RES
S1: SWITCH-MOMENTARY-LEDPTH; TACTILE-PTH-LED-12MM
S2, S3: SWITCH-MOM-4.5
U1: E0_V005; E0
U$3: USB-MICRO-B-SOCKET-AMPHENOL; USB-B-SMT-AMPHENOL

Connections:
3V3: LED1.1 (A), LED2.1 (A), R5.2, U1.9 (3V3), U1.10 (VDDA), U1.11 (VBAT)
/MODE: S2.3, U1.55 (!MODE)
/RESET: R5.1, S3.3, U1.56 (!RESET)
BLED: LED1.2 (B), R3.2
BLUE: R8.2, U1.52 (BLUE)
D2: R3.1, U1.40 (D2)
D3: R2.1, U1.39 (D3)
D4: S1.A, U1.38 (D4)
D5: S1.4 (1), U1.37 (D5)
D+: U1.13 (USB+), U$3.3 (D+)
D-: U1.14 (USB-), U$3.2 (D-)
GLED: LED1.3 (G), R2.2
GND: CN1.2 (1), JP1.2, R4.2, S1.2, S2.2, S3.2, U1.2 (GND), U1.4 (GND), U1.7 (GND), U1.12 (GND), U1.15 (GND), U1.18 (GND), U1.27 (GND), U1.34 (GND), U1.43 (GND), U1.51 (GND), U1.58 (GND), U1.59 (GND), U1.60 (GND), U$3.5 (GND)
GREEN: R7.2, U1.53 (GREEN)
LIPO: CN1.1 (2), U1.5 (LIPO)
unnamed: LED2.3 (G), R7.1
unnamed: LED2.4 (R), R6.1
unnamed: LED2.2 (B), R8.1
RED: R6.2, U1.54 (RED)
RLED: LED1.4 (R), R1.2
SLED: R4.1, S1.C
VBUS: U1.3 (VBUS), U$3.1 (VBUS)
VIN: JP1.1, U1.1 (VIN)
WKP: R1.1, U1.19 (WKP)

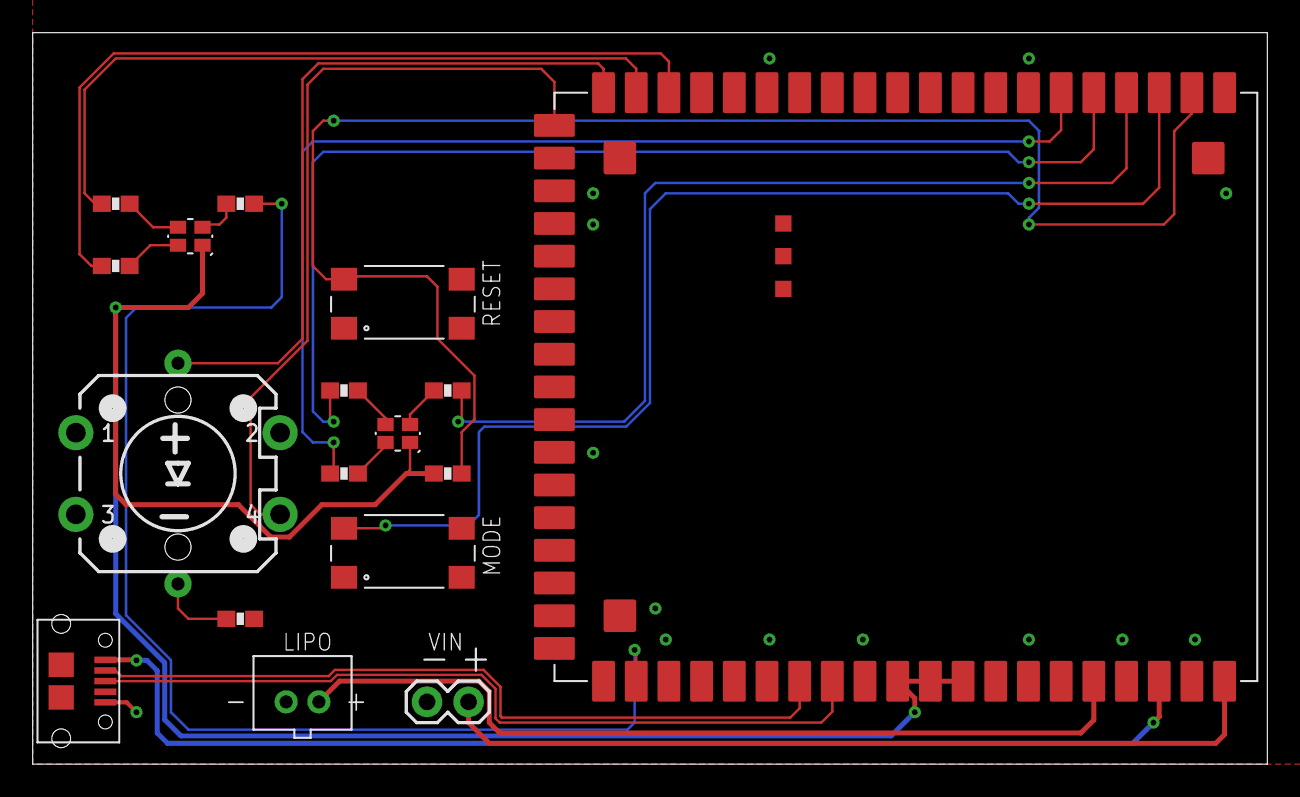
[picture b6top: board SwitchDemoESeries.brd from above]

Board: 2 copper layers, 75.5 x 44.8 mm, 17 parts (0 on the bottom side), 24 nets.

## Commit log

2019-07-12 som-first-board
2019-10-24 Update M.2 standoff
2019-12-16 Add beyond prototyping tutorial content
2020-03-30 SoM First Board v2
    Changed value of R8
2024-01-22 v3
    - Swap pins D2 and D3

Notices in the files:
parts and their libraries:
Particle-Devices: Licensing: Designed by Particle.
SparkFun-Electromechanical: Licensing: Creative Commons ShareAlike 4.0 International - https://creativecommons.org/licenses/by-sa/4.0
